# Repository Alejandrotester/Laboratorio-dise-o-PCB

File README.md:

# Laboratorio de Diseño Electrónico CAD — KiCad 10

**Curso:** Diseño Electrónico CAD  
**Autores:** Alejandro Beltrán Cardona, Daniel Zuluaga González y Jhon Alexander Salazar Rendón.  
**Fecha:** octubre de 2026.

## Contenido

- `Ejercicio_1_Linterna/`: linterna LED alimentada con pila CR2032, pulsador y resistencia limitadora.
- `Ejercicio_2_ESP32_S3_Mini/`: tarjeta compacta ESP32-S3 con regulación AMS1117-3.3, botón BOOT y USB.
- `Ejercicio_3_ESP32_S3_USB_C_PCBA/`: placa ESP32-S3 avanzada con USB-C, CP2102N, protección ESD, autoprogramación y conectores GPIO.

Todos los proyectos son de **dos capas de cobre**. Cada carpeta incluye los archivos `.kicad_pro`, `.kicad_sch` y `.kicad_pcb` originales. El ejercicio 2 incluye además la biblioteca de símbolo y huella personalizada, configurada con rutas relativas al proyecto.

## Cómo abrir

1. Instalar KiCad 10.x.
2. Entrar en la carpeta del ejercicio deseado.
3. Abrir el archivo `.kicad_pro` correspondiente.
4. Para revisar los circuitos y las placas, usar el editor esquemático y el editor PCB.
5. Antes de fabricar, ejecutar ERC/DRC con las reglas compatibles con el fabricante y comprobar las exclusiones o pruebas ignoradas.

## Fabricación y ensamblaje

Los archivos Gerber/Excellon se exportan desde el editor PCB de cada ejercicio. La tarjeta 3 también requiere BOM y CPL/posiciones para la cotización PCBA. **Este repositorio incluye los proyectos fuente; no implica que se hayan fabricado físicamente, comprado o ensamblado las tarjetas.**

El importe de fabricación depende de las especificaciones y de la cotización actual de JLCPCB. Verifique límites de manufactura, el manejo de la antena RF y la coincidencia real entre BOM, componentes disponibles y huellas.

## Nota

No se incluyen las carpetas `.history/.git` (historial local de la herramienta), archivos de sesión `.kicad_prl`, copias de seguridad o binarios temporales. El circuito y la PCB no se han modificado en el proceso de organización del repositorio.

## Cotizaciones JLCPCB: 27 de octubre de 2026

Captura: `Cotizaciones_JLCPCB/cotizacion_carrito_jlcpcb_27_10_2026.png`.

| Concepto | 5 unidades | Precio observado (USD) |
|---|---:|---:|
| PCB linterna LED | 5 | 20,66 |
| PCB ESP32-S3 Mini | 5 | 4,00 |
| PCB ESP32-S3 USB-C | 5 | 4,00 |
| PCBA estándar SMT superior ESP32-S3 USB-C | 5 | 123,36 |
| **Suma de partidas visibles** | | **152,02** |

El precio de PCBA indica *Assemble top side* y no demuestra montaje completo de pines/pulsadores THT o ensamblaje inferior. Valores sin verificación de envío e impuestos. La cotización no es un pedido pagado.

El informe IEEE actualizado se encuentra en `Informe_IEEE/`.

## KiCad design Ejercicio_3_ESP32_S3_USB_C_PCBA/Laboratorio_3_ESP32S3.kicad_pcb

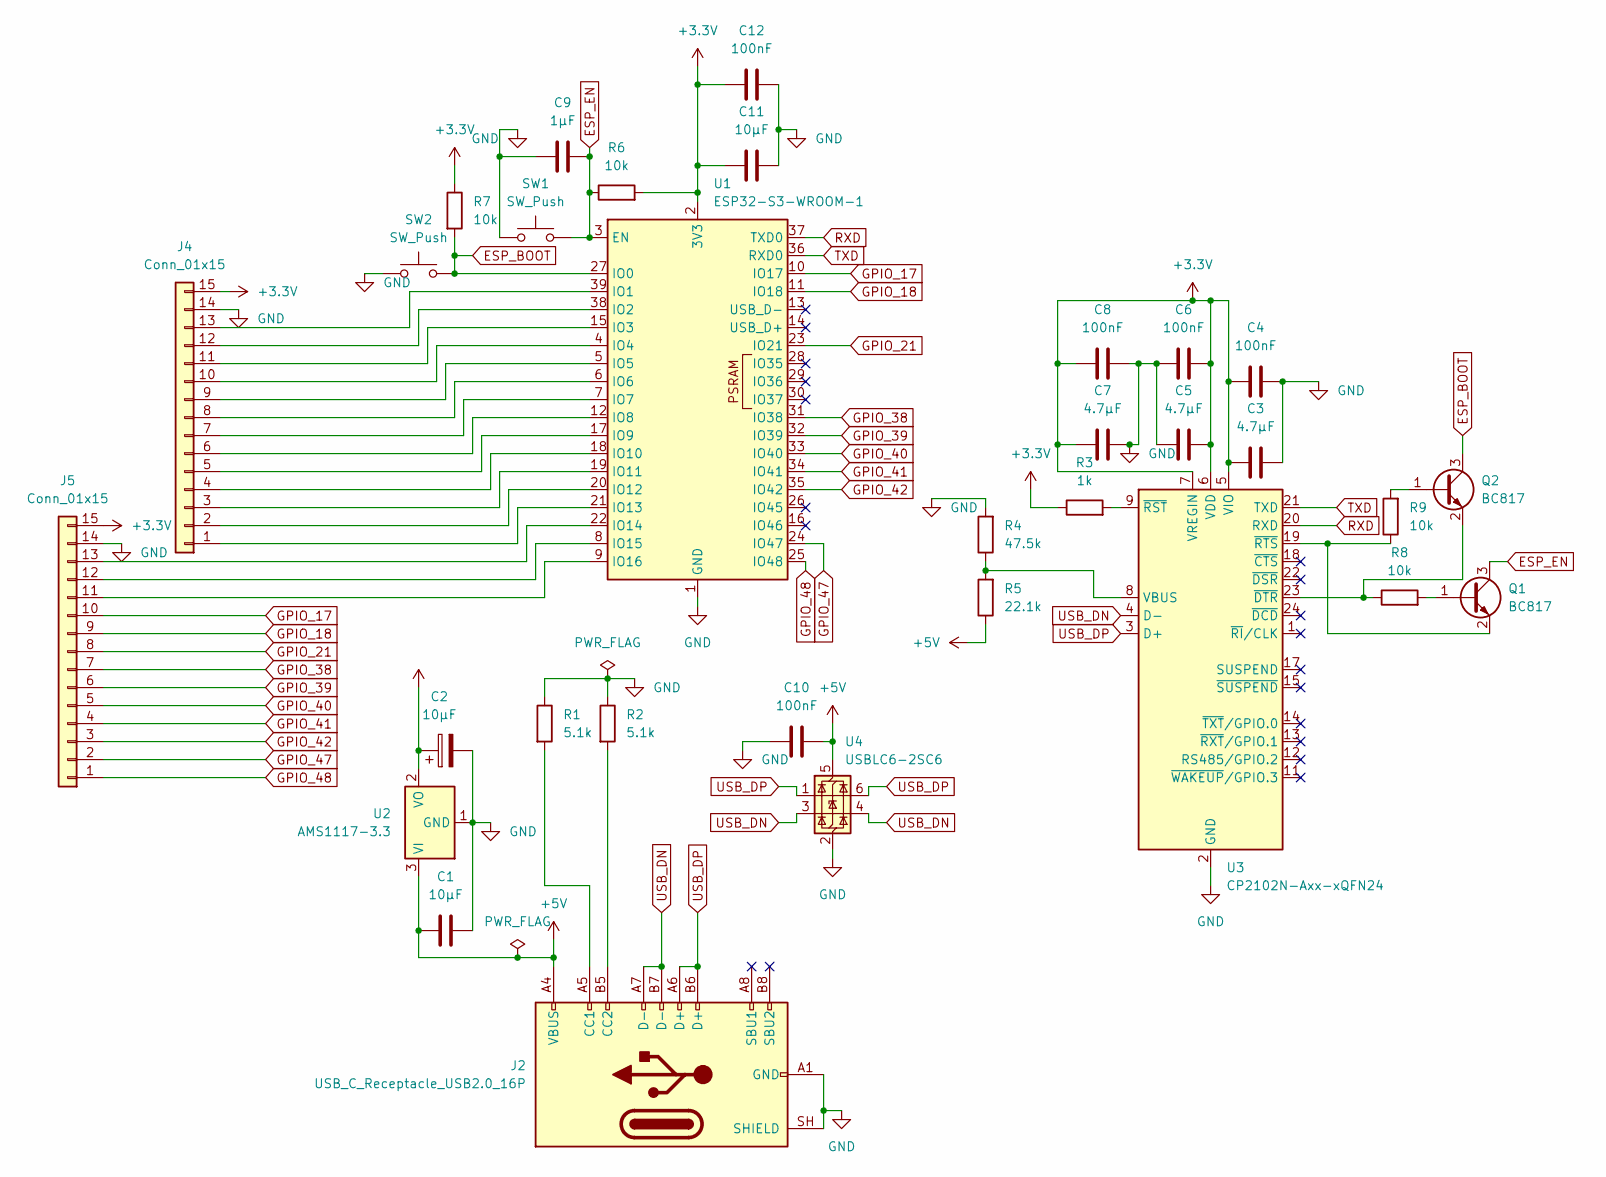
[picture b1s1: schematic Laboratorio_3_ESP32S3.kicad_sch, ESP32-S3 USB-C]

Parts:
C1, C11: 10µF; C_1206_3216Metric
C2: 10µF; CP_EIA-3216-18_Kemet-A
C3, C5, C7: 4.7µF; C_0805_2012Metric
C4, C6, C8, C10, C12: 100nF; C_0603_1608Metric
C9: 1µF; C_0805_2012Metric
J2: USB_C_Receptacle_USB2.0_16P; USB_C_Receptacle_GCT_USB4105-xx-A_16P_TopMnt_Horizontal
J4, J5: Conn_01x15; PinHeader_1x15_P2.54mm_Vertical
Q1, Q2: BC817; SOT-23
R1, R2: 5.1k; R_0805_2012Metric
R3: 1k; R_0805_2012Metric
R4: 47.5k; R_0805_2012Metric
R5: 22.1k; R_0805_2012Metric
R6, R7, R8, R9: 10k; R_0805_2012Metric
SW1, SW2: SW_Push; SW_PUSH_6mm
U1: ESP32-S3-WROOM-1
U2: AMS1117-3.3; SOT-223-3_TabPin2
U3: CP2102N-Axx-xQFN24; QFN-24-1EP_4x4mm_P0.5mm_EP2.6x2.6mm
U4: USBLC6-2SC6; SOT-23-6

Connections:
+3.3V: C2.1, C3.2, C4.1, C5.1, C6.2, C7.2, C8.1, C11.1, C12.1, J4.15, J5.15, R3.1, R6.2, R7.1, U1.2 (3V3), U2.2 (VO), U3.5 (VIO), U3.6 (VDD), U3.7 (VREGIN)
+5V: C1.1, C10.2, J2.A4 (VBUS), J2.A9 (VBUS), J2.B4 (VBUS), J2.B9 (VBUS), R5.1, U2.3 (VI), U4.5 (VBUS)
ESP_BOOT: Q2.3 (C), R7.2, SW2.2, U1.27 (IO0)
ESP_EN: C9.2, Q1.3 (C), R6.1, SW1.2, U1.3 (EN)
GND: C1.2, C2.2, C3.1, C4.2, C5.2, C6.1, C7.1, C8.2, C9.1, C10.1, C11.2, C12.2, J2.A1 (GND), J2.A12 (GND), J2.B1 (GND), J2.B12 (GND), J2.SH (SHIELD), J4.14, J5.14, R1.1, R2.1, R4.2, SW1.1, SW2.1, U1.1 (GND), U1.40 (GND), U1.41 (GND), U2.1 (GND), U3.2 (GND), U3.25 (GND), U4.2 (GND)
GPIO_17: J5.10, U1.10 (IO17)
GPIO_18: J5.9, U1.11 (IO18)
GPIO_21: J5.8, U1.23 (IO21)
GPIO_38: J5.7, U1.31 (IO38)
GPIO_39: J5.6, U1.32 (IO39)
GPIO_40: J5.5, U1.33 (IO40)
GPIO_41: J5.4, U1.34 (IO41)
GPIO_42: J5.3, U1.35 (IO42)
GPIO_47: J5.2, U1.24 (IO47)
GPIO_48: J5.1, U1.25 (IO48)
unnamed: J2.A5 (CC1), R1.2
unnamed: J2.B5 (CC2), R2.2
unnamed: J4.1, U1.21 (IO13)
unnamed: J4.2, U1.20 (IO12)
unnamed: J4.3, U1.19 (IO11)
unnamed: J4.4, U1.18 (IO10)
unnamed: J4.5, U1.17 (IO9)
unnamed: J4.6, U1.12 (IO8)
unnamed: J4.7, U1.7 (IO7)
unnamed: J4.8, U1.6 (IO6)
unnamed: J4.9, U1.5 (IO5)
unnamed: J4.10, U1.4 (IO4)
unnamed: J4.11, U1.15 (IO3)
unnamed: J4.12, U1.38 (IO2)
unnamed: J4.13, U1.39 (IO1)
unnamed: J5.11, U1.9 (IO16)
unnamed: J5.12, U1.8 (IO15)
unnamed: J5.13, U1.22 (IO14)
unnamed: Q1.1 (B), R8.2
unnamed: Q1.2 (E), R9.1, U3.19 (~RTS)
unnamed: Q2.1 (B), R9.2
unnamed: Q2.2 (E), R8.1, U3.23 (~DTR)
unnamed: R4.1, R5.2, U3.8 (VBUS)
unnamed: R3.2, U3.9 (~RST)
RXD: U1.37 (TXD0), U3.20 (RXD)
TXD: U1.36 (RXD0), U3.21 (TXD)
USB_DN: J2.A7 (D-), J2.B7 (D-), U3.4 (D-), U4.3 (I/O2), U4.4 (I/O2)
USB_DP: J2.A6 (D+), J2.B6 (D+), U3.3 (D+), U4.1 (I/O1), U4.6 (I/O1)

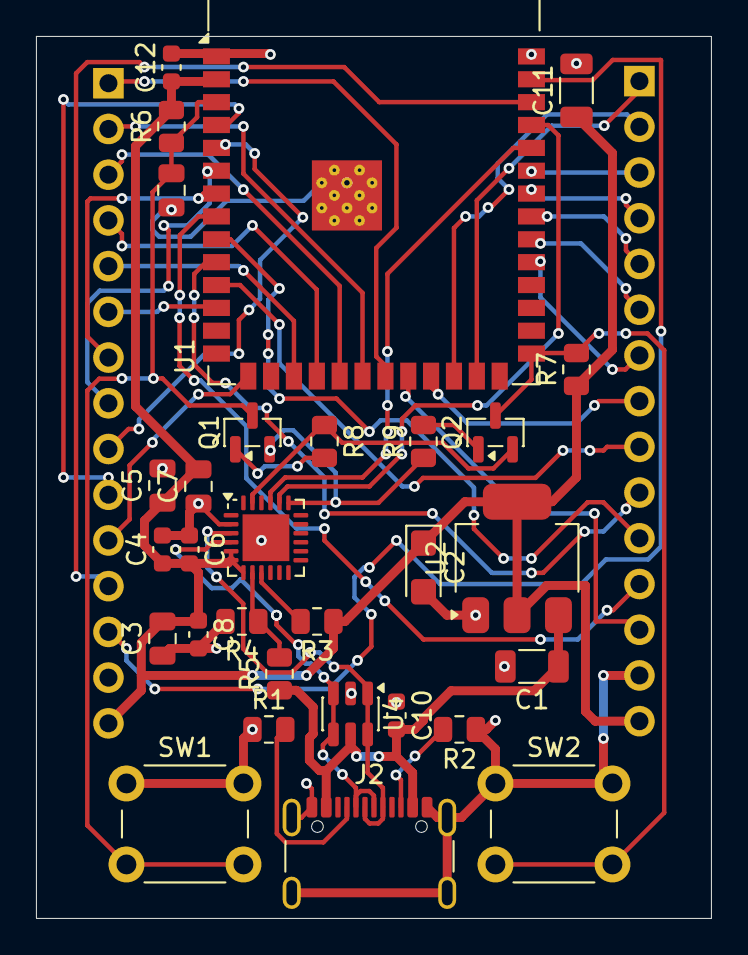
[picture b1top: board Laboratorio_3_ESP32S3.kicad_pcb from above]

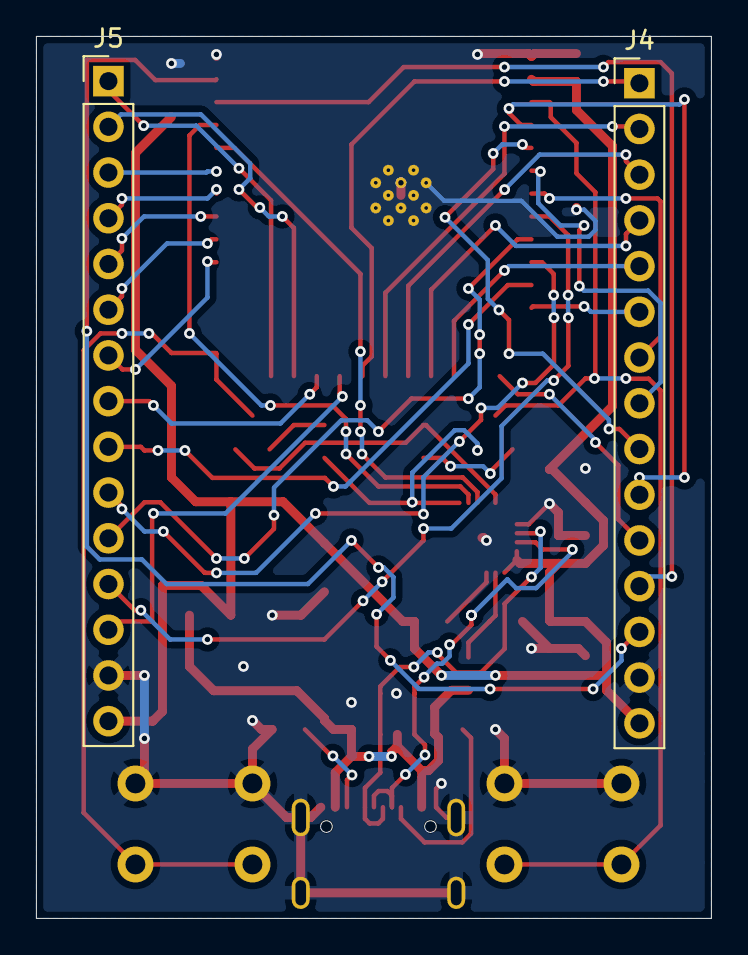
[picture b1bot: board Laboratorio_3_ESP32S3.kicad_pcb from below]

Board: 2 copper layers, 37.5 x 49.0 mm, 32 parts (2 on the bottom side), 43 nets.

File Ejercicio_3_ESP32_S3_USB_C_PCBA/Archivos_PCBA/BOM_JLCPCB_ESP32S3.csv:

Comment,Designator,Footprint,JLCPCB Part #
10uF,"C1,C11",1206,
10uF,C2,CP_EIA-3216-18_Kemet-A,
4.7uF,"C3,C5,C7",0805,
100nF,"C4,C6,C8,C10,C12",0603,
1uF,C9,0805,
USB_C_Receptacle_USB2.0_16P,J2,USB_C_Receptacle_GCT_USB4105-xx-A_16P_TopMnt_Horizontal,
Conn_01x15,"J4,J5",PinHeader_1x15_P2.54mm_Vertical,
BC817,"Q1,Q2",SOT-23,
5.1k,"R1,R2",0805,
1k,R3,0805,
47.5k,R4,0805,
22.1k,R5,0805,
10k,"R6,R7,R8,R9",0805,
SW_Push,"SW1,SW2",SW_PUSH_6mm,
ESP32-S3-WROOM-1,U1,ESP32-S3-WROOM-1,
AMS1117-3.3,U2,SOT-223-3_TabPin2,
CP2102N-Axx-xQFN24,U3,QFN-24-1EP_4x4mm_P0.5mm_EP2.6x2.6mm,
USBLC6-2SC6,U4,SOT-23-6,

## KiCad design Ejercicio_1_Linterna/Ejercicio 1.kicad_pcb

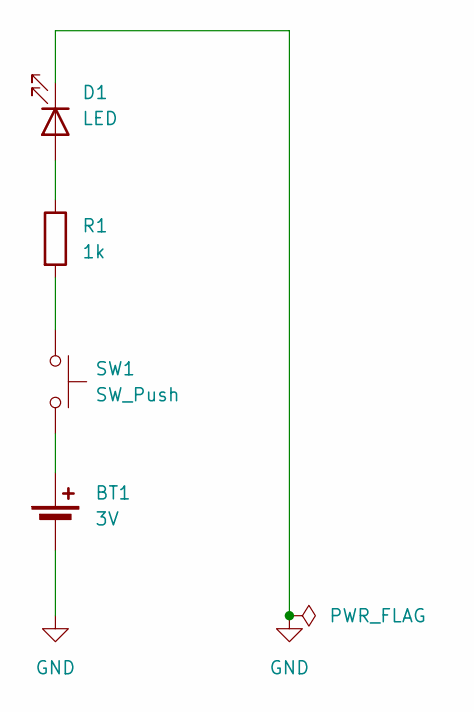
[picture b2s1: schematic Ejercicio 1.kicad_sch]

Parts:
BT1: 3V; BatteryHolder_Keystone_3034_1x20mm
D1: LED; LED_D5.0mm
R1: 1k; R_0805_2012Metric
SW1: SW_Push; SW_PUSH_6mm

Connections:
GND: BT1.2 (-), D1.1 (K)
unnamed: BT1.1 (+), SW1.2
unnamed: D1.2 (A), R1.1
unnamed: R1.2, SW1.1

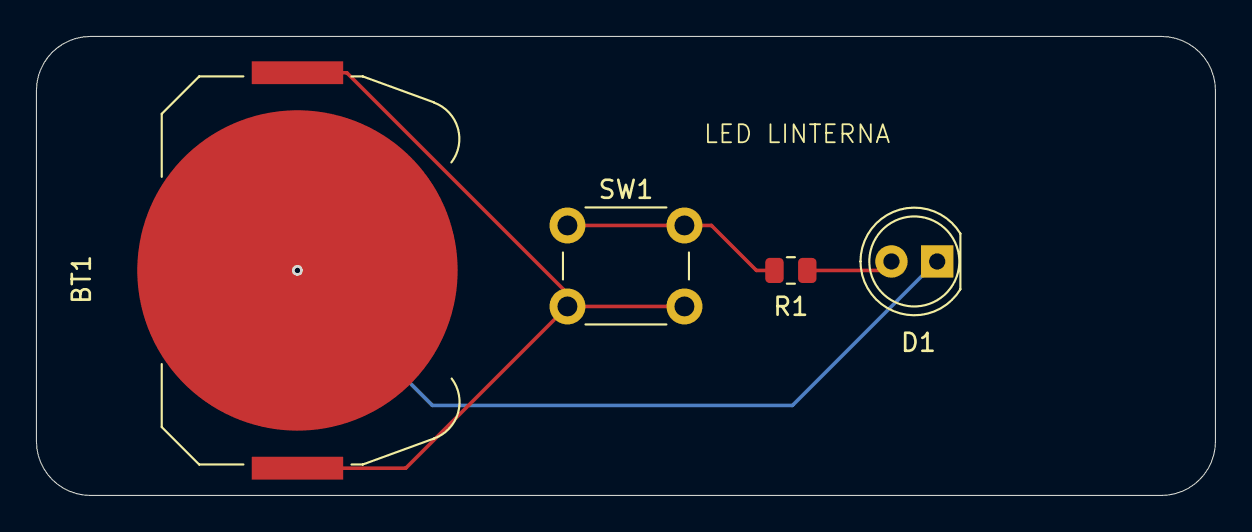
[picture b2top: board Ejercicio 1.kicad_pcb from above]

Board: 2 copper layers, 65.5 x 25.5 mm, 4 parts (0 on the bottom side), 4 nets.

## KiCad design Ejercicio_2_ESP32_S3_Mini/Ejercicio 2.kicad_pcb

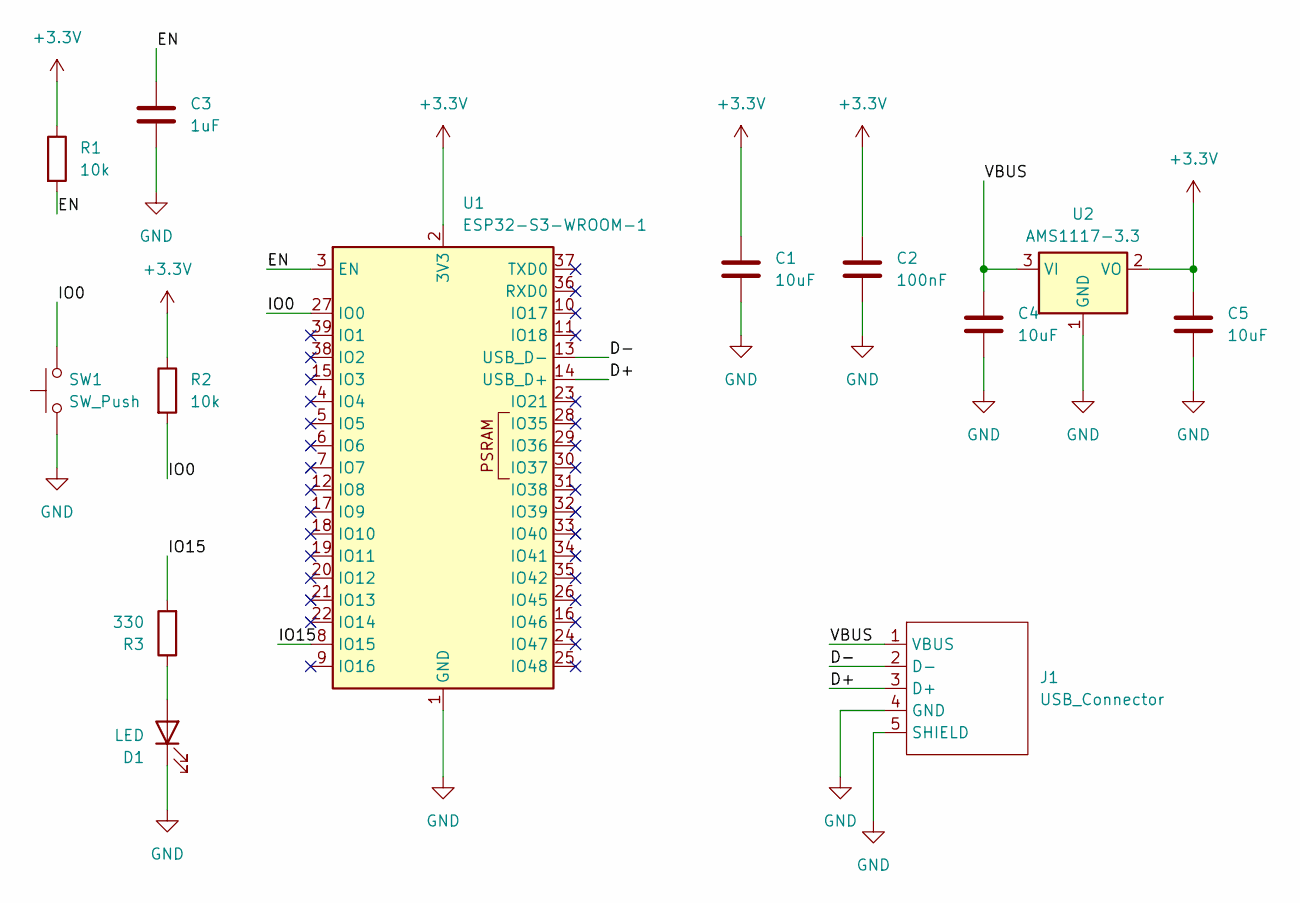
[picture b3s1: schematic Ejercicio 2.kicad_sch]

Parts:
C1, C4, C5: 10uF; C_0805_2012Metric
C2: 100nF; C_0805_2012Metric
C3: 1uF; C_0805_2012Metric
D1: LED; LED_0805_2012Metric
J1: USB_Connector; USB_Custom
R1, R2: 10k; R_0805_2012Metric
R3: 330; R_0805_2012Metric
SW1: SW_Push; SW_PUSH_6mm
U1: ESP32-S3-WROOM-1
U2: AMS1117-3.3; SOT-223-3_TabPin2

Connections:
+3.3V: C1.1, C2.1, C5.1, R1.1, R2.1, U1.2 (3V3), U2.2 (VO)
/D+: J1.3 (D+), U1.14 (USB_D+)
/D-: J1.2 (D-), U1.13 (USB_D-)
/EN: C3.1, R1.2, U1.3 (EN)
/IO0: R2.2, SW1.2, U1.27 (IO0)
/IO15: R3.2, U1.8 (IO15)
/VBUS: C4.1, J1.1 (VBUS), U2.3 (VI)
GND: C1.2, C2.2, C3.2, C4.2, C5.2, D1.1 (K), J1.4 (GND), J1.5 (SHIELD), SW1.1, U1.1 (GND), U1.40 (GND), U1.41 (GND), U2.1 (GND)
unnamed: D1.2 (A), R3.1

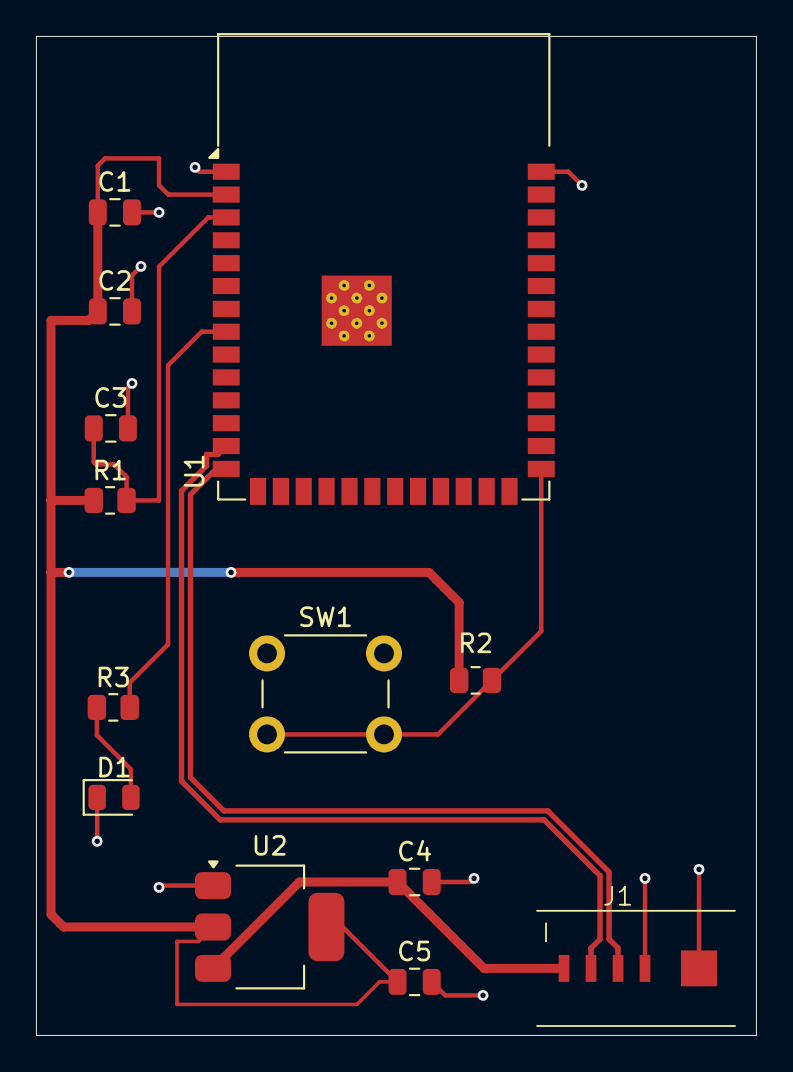
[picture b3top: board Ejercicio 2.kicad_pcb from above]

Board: 2 copper layers, 40.0 x 55.5 mm, 13 parts (0 on the bottom side), 9 nets.
